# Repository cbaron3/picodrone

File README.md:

# picodrone

Micro drone project using STM32

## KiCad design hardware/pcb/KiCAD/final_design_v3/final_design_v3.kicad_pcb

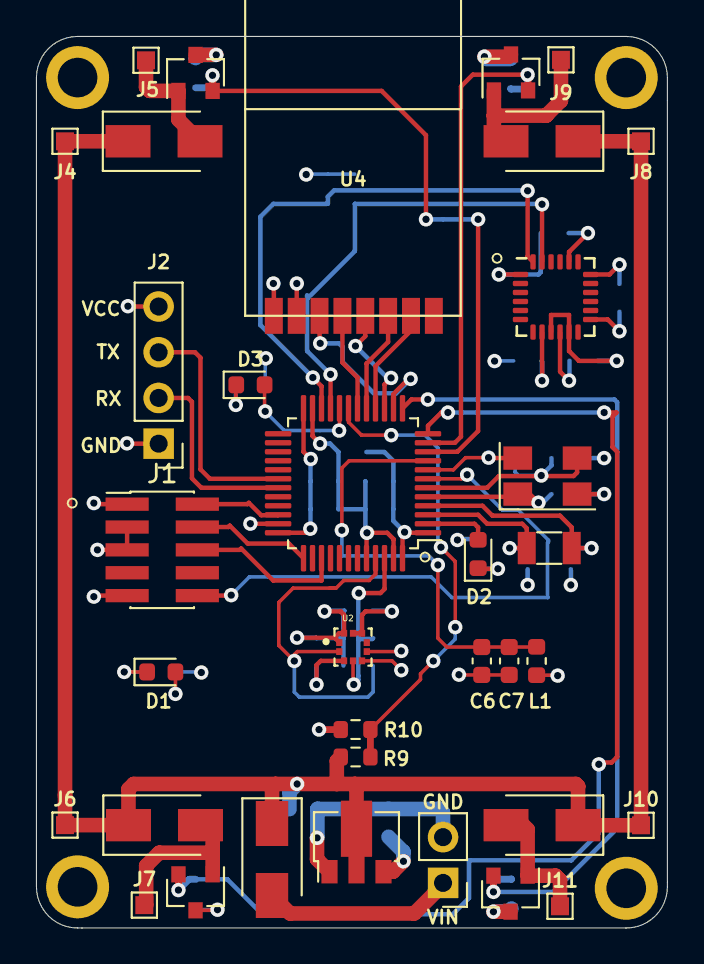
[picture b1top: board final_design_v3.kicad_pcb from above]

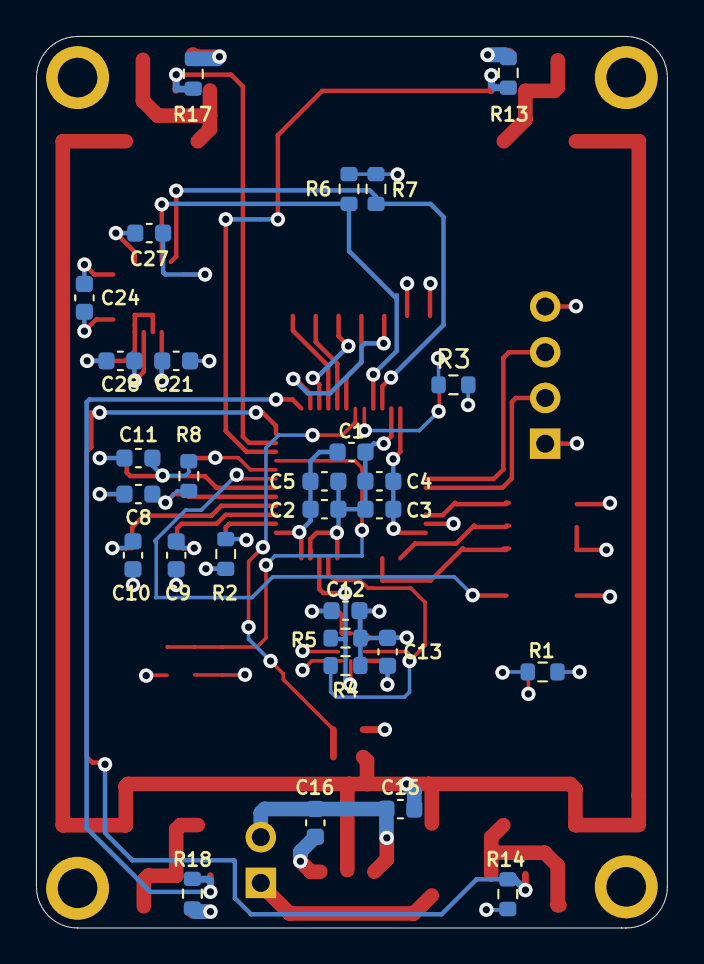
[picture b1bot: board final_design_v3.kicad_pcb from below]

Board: 4 copper layers, 35.1 x 49.5 mm, 68 parts (29 on the bottom side), 41 nets.

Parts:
C1: 4.7u; C_0603_1608Metric
C2, C3, C4, C5, C12, C13, C24, C28: 100n; C_0603_1608Metric
C6: 1u; C_0603_1608Metric
C7, C21: 10n; C_0603_1608Metric
C8, C11: 15p; C_0603_1608Metric
C9, C10: 10p; C_0603_1608Metric
C15, C16: 10u; C_0603_1608Metric
C27: 2.2n; C_0603_1608Metric
D1: Green; LED_0603_1608Metric
D2: Yellow; LED_0603_1608Metric
D3: Blue; LED_0603_1608Metric
D5, D6, D7, D8, D9: D_Schottky; D_SMA
H1, H2, H3, H4: MntHole; MountingHole_2.2mm_M2_ISO7380_Pad
J1: ARM SWD 10p; PinHeader_2x05_P1.27mm_Vertical_SMD
J2: Conn_01x04; PinHeader_1x04_P2.54mm_Vertical
J3: Conn_01x02; PinHeader_1x02_P2.54mm_Vertical
J4: M1+; TestPoint_Pad_1.0x1.0mm
J5: M1-; TestPoint_Pad_1.0x1.0mm
J6: M2+; TestPoint_Pad_1.0x1.0mm
J7: M2-; TestPoint_Pad_1.0x1.0mm
J8: M3+; TestPoint_Pad_1.0x1.0mm
J9: M3-; TestPoint_Pad_1.0x1.0mm
J10: M4+; TestPoint_Pad_1.0x1.0mm
J11: M4-; TestPoint_Pad_1.0x1.0mm
L1: 33n; L_0603_1608Metric
Q1, Q2, Q3, Q4: SI2302; SOT-23
R1, R2, R3: 1k; R_0603_1608Metric
R4, R5, R6, R7: 4.7k; R_0603_1608Metric
R8: 1M; R_0603_1608Metric
R9, R10: 100k; R_0603_1608Metric
R13, R14, R17, R18: 10k; R_0603_1608Metric
U1: STM32F103C8Tx; LQFP-48_7x7mm_P0.5mm
U2: BMP388; PQFN50P200X200X80-10N
U3: HT7333; SOT-89-3
U4: NRF24L01; NRF24L01-SMD
U5: MPU-6050; InvenSense_QFN-24_4x4mm_P0.5mm
Y1: 32.768 kHz; Crystal_SMD_3215-2Pin_3.2x1.5mm
Y2: 8 MHz; Crystal_SMD_5032-4Pin_5.0x3.2mm

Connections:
+3.3VA: C6.1, C7.1, L1.2, U1.9
+3V3: C1.1, C2.1, C3.1, C4.1, C5.1, C12.1, C13.2, C16.2, C21.1, C24.2, D1.2, J1.1, J2.4, L1.1, R4.1, R5.1, R6.1, R7.1, U1.1, U1.24, U1.36, U1.48, U2.1, U2.6, U2.10, U3.3, U4.2, U5.8, U5.13
+BATT: D5.2, J3.1
ADC_BATT: R9.1, R10.2, U1.19
GND: C1.2, C2.2, C3.2, C4.2, C5.2, C6.2, C7.2, C8.1, C9.1, C10.1, C11.1, C12.2, C13.1, C15.1, C16.1, C21.2, C24.1, C27.1, C28.2, H1.1, H2.1, H3.1, H4.1, J1.3, J1.5, J1.9, J2.1, J3.2, Q1.3, Q2.3, Q3.3, Q4.3, R1.1, R2.1, R3.1, R10.1, R13.1, R14.1, R17.1, R18.1, U1.8, U1.23, U1.35, U1.44, U1.47, U2.3, U2.5, U2.8, U2.9, U3.1, U4.1, U5.1, U5.9, U5.11, U5.18, Y2.2, Y2.4
I2C1_SCL: R4.2, U1.45, U2.2
I2C1_SDA: R5.2, U1.46, U2.4
I2C2_SCL: R6.2, U1.21, U5.23
I2C2_SDA: R7.2, U1.22, U5.24
LED1: D2.2, U1.2
LED2: D3.2, U1.20
M1_PWM: Q1.2, R13.2, U1.10
M2_PWM: Q3.2, R17.2, U1.11
M3_PWM: Q2.2, R14.2, U1.12
M4_PWM: Q4.2, R18.2, U1.13
NRST: J1.10, U1.7
unnamed: C27.2, U5.20
unnamed: C28.1, U5.10
unnamed: D1.1, R1.2
unnamed: D2.1, R2.2
unnamed: D3.1, R3.2
unnamed: D6.2, J5.1, Q1.1
unnamed: D7.2, J7.1, Q2.1
unnamed: D8.2, J9.1, Q3.1
unnamed: D9.2, J11.1, Q4.1
OSC8_IN: C8.2, R8.2, U1.5, Y2.1
OSC8_OUT: C11.2, R8.1, U1.6, Y2.3
OSC32_IN: C9.2, U1.3, Y1.1
OSC32_OUT: C10.2, U1.4, Y1.2
SPI1_CE: U1.14, U4.3
SPI1_CSN: U1.18, U4.4
SPI1_IRQ: U1.33, U4.8
SPI1_MISO: U1.16, U4.7
SPI1_MOSI: U1.17, U4.6
SPI1_SCK: U1.15, U4.5
SWCLK: J1.4, U1.37
SWDIO: J1.2, U1.34
SWO: J1.6, U1.39
UART1_RX: J2.2, U1.31
UART1_TX: J2.3, U1.30
VCC: C15.2, D5.1, D6.1, D7.1, D8.1, D9.1, J4.1, J6.1, J8.1, J10.1, R9.2, U3.2

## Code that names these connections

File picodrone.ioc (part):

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Mcu.Name=STM32F103C(8-B)Tx
Mcu.Package=LQFP48
Mcu.UserName=STM32F103C8Tx
PA10.Mode=Asynchronous
PA10.Signal=USART1_RX
PA13.Mode=JTAG_4_pins
PA13.Signal=SYS_JTMS-SWDIO
PA14.Mode=JTAG_4_pins
PA14.Signal=SYS_JTCK-SWCLK
PA15.Mode=JTAG_4_pins
PA15.Signal=SYS_JTDI
PA5.Mode=Full_Duplex_Master
PA5.Signal=SPI1_SCK
PA6.Mode=Full_Duplex_Master
PA6.Signal=SPI1_MISO
PA7.Mode=Full_Duplex_Master
PA7.Signal=SPI1_MOSI
PA9.Mode=Asynchronous
PA9.Signal=USART1_TX
PB0.Signal=GPIO_Output
PB1.Signal=GPIO_Output
PB3.Mode=JTAG_4_pins
PB3.Signal=SYS_JTDO-TRACESWO
PC13-TAMPER-RTC.Signal=GPIO_Output
PD0-OSC_IN.Mode=HSE-External-Oscillator
PD0-OSC_IN.Signal=RCC_OSC_IN
PD1-OSC_OUT.Mode=HSE-External-Oscillator
PD1-OSC_OUT.Signal=RCC_OSC_OUT
RCC.SYSCLKFreq_VALUE=72000000
RCC.SYSCLKSource=RCC_SYSCLKSOURCE_PLLCLK
board=custom

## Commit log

2020-10-27 Initial project structure
2020-10-28 Startup script + linker file complete. Tested in other project with STM32 dependencies linked
2020-11-01 blink and basic pwm code working
2020-11-01 confirmed using cpp works in current build system
2020-11-03 interface refactor & add FreeRTOS to build system
2020-11-05 cpp freertos added
2020-11-05 dependency cleanup
2020-11-05 more dependency cleanup
2020-11-05 finalized dependency clean up
2020-11-05 reverted back to C interface; think it is much much cleaner
2020-11-05 adding uart
2020-11-05 freertos tasks setusp
2020-11-06 USART1 confirmed working with oscilloscope
2020-11-06 Reduced flash usage by 30k (~50%) by changing from HAL_TIM to LL_TIM
2020-11-07 more memory size debugging
2020-11-07 Basic xQueue send/receive w/ FreeRTOS
2020-11-08 Basic I2C working with BMP180, heavy refactor needed
2020-11-09 attempt to create cleaner interface, code left commented out cause won't compile
2020-11-13 code abstraction work, temp
2020-11-13 basic hardware setup
2020-11-15 completed mosfet test pcb used for testing V, I characteristics of different sot23 fets
2020-11-19 pcb work
2020-11-21 board renaming
2020-11-26 added nrf24 smt to i2c test board
2020-11-27 Schematic finalized (besides crystal load c ap and resistor values)
2020-11-27 schematic updates
2020-11-28 Replaced BMP280 w/ BMP388 cause of stock availability and another tweaks to schematic
2020-11-29 Schematic finished, BOM verified
2020-11-29 finalized circuit boards and ordered w/ gerber files
2020-12-04 minor cleanup
2020-12-07 started file restructure, trying to get new task base working
2020-12-11 Finished restructure, just need to split common into H and C files or inline/static all functions/variables
2020-12-11 Trying to get lib components working, at least got queue to be passed in as param
2020-12-12 Completed restructure with tasks in individual projects
2020-12-13 Working on cleaner interface, UART working with LL now
2020-12-13 i2c not working now
2020-12-13 magically fixed the i2c issue by moving init to task scope instead of main scope
2020-12-14 MPU working, SPI next
2020-12-14 Validated NRF24 connection by configuring settings correctly. Had to use library to make it easy
2020-12-15 Some more validation
2020-12-28 NRF test, that failed
2021-02-28 updated board design
2021-02-28 Include mini NRF24 library
2021-03-07 Updated 4-layer design with NRF24 module instead of actual chip
2021-03-10 Stripped old code for fresh start
2021-03-13 Started refactor on controller
2021-03-19 Simple dockerfile with script that allows for basic build process
2021-03-20 Added clean build to build script
2021-03-20 Added python script functionality
2021-03-20 Added elf size tracking to build process with persistent memory
2021-03-21 Script clean up
2021-03-21 Completed elf size tracking using python script for both transmitter and drone
2021-03-21 Included dockerfile for hardware file auto-generation (images)
2021-03-24 Build process refined
2021-05-19 controller init refactor using C instead of C++ interface. works with v3 board
2021-05-20 UART confirmed working on v3
2021-05-20 pushing v3 board to repo
2022-05-16 Start from scratch, already proved can now get NRF24 working with STM32
